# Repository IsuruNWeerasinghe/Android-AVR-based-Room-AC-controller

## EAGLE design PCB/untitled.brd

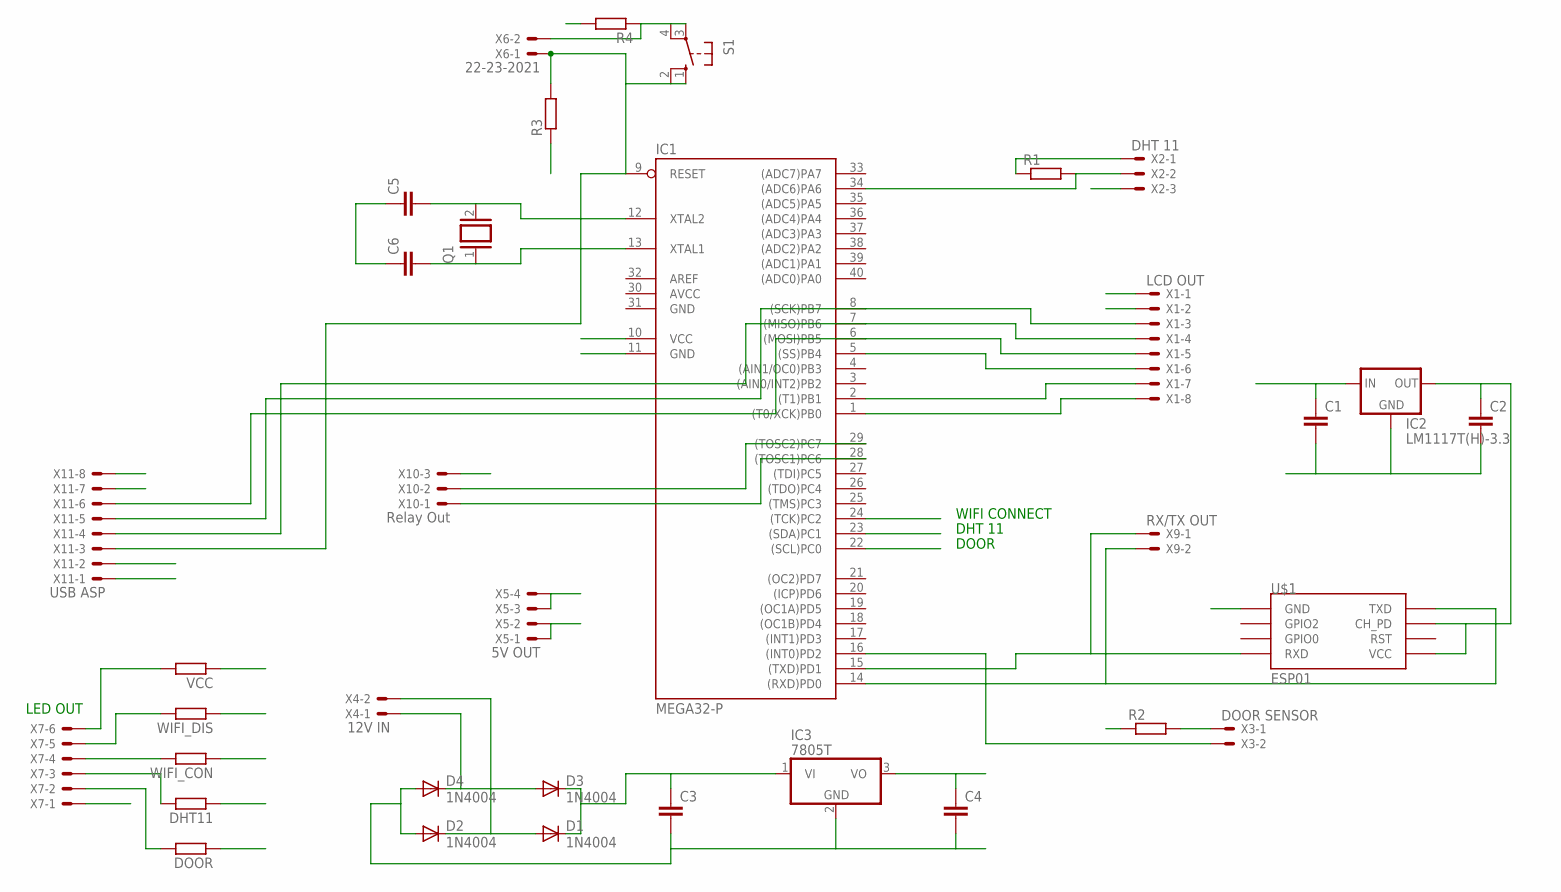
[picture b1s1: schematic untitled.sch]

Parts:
C1, C2, C4: C2.5/2; C2.5-2
C3: C5/2.5; C5B2.5
C5, C6: C-EU025-025X050; C025-025X050
D1, D2, D3, D4: 1N4004; DO41-10
DHT11: R-EU_0204/7; 0204/7
DOOR: R-EU_0204/7; 0204/7
IC1: MEGA32-P; DIL40
IC2: LM1117T(H)-3.3; TO220H
IC3: 7805T; TO220H
Q1: XTAL/S; QS
R1, R2, R3, R4: R-EU_0204/7; 0204/7
S1: 10-XX; B3F-10XX
U$1: ESP01
VCC: R-EU_0204/7; 0204/7
WIFI_CON: R-EU_0204/7; 0204/7
WIFI_DIS: R-EU_0204/7; 0204/7
X1: LCD OUT; 22-23-2081
X2: DHT 11; 22-23-2031
X3: DOOR SENSOR; 22-23-2021
X4: 12V IN; 22-23-2021
X5: 5V OUT; 22-23-2041
X6: 22-23-2021
X7: 22-23-2061
X9: RX/TX OUT; 22-23-2021
X10: Relay Out; 22-23-2031
X11: USB ASP; 22-23-2081

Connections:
12LINE1: D3.A, D4.C, X4.1
12LINE2: D1.A, D2.C, X4.2
AVCC: IC1.30 (AVCC)
DHT11: DHT11.1, IC1.23 ((SDA)PC1)
DOOR: DOOR.1, IC1.22 ((SCL)PC0)
GND: C1.2, C2.2, C3.2, C4.2, C5.1, C6.1, D2.A, D4.A, IC1.11 (GND), IC1.31 (GND), IC2.1 (GND), IC3.2 (GND), R3.1, U$1.GND, X1.2, X2.3, X5.1, X5.2, X7.1, X10.3, X11.7
unnamed: IC1.8 ((SCK)PB7), X1.3, X11.5
unnamed: IC1.7 ((MISO)PB6), X1.4, X11.4
unnamed: IC1.6 ((MOSI)PB5), X1.5, X11.6
unnamed: IC1.5 ((SS)PB4), X1.6
unnamed: IC1.2 ((T1)PB1), X1.7
unnamed: IC1.1 ((T0/XCK)PB0), X1.8
unnamed: IC1.34 ((ADC6)PA6), R1.2, X2.2
unnamed: R2.2, X3.1
unnamed: IC1.9 (RESET), R3.2, S1.1 (S), S1.2 (S1), X6.1, X11.3
unnamed: IC1.16 ((INT0)PD2), X3.2
unnamed: IC1.28 ((TOSC1)PC6), X10.1
unnamed: IC1.29 ((TOSC2)PC7), X10.2
unnamed: C2.1, IC2.2 (OUT), U$1.CH_PD, U$1.VCC
unnamed: C5.2, IC1.12 (XTAL2), Q1.2
unnamed: C6.2, IC1.13 (XTAL1), Q1.1
unnamed: C3.1, D1.C, D3.C, IC3.1 (VI)
unnamed: VCC.2, X7.6
unnamed: WIFI_DIS.2, X7.5
unnamed: WIFI_CON.2, X7.4
unnamed: DHT11.2, X7.3
unnamed: DOOR.2, X7.2
unnamed: R4.1, S1.3, S1.4 (P1), X6.2
RXD: IC1.14 ((RXD)PD0), U$1.TX (TXD), X9.2, X11.2
TXD: IC1.15 ((TXD)PD1), U$1.RX (RXD), X9.1, X11.1
VCC: C1.1, C4.1, IC1.10 (VCC), IC2.3 (IN), IC3.3 (VO), R1.1, R2.1, R4.2, VCC.1, WIFI_DIS.1, X1.1, X2.1, X5.3, X5.4, X11.8
WIFI: IC1.24 ((TCK)PC2), WIFI_CON.1

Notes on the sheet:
WIFI CONNECT
DHT 11
DOOR
LED OUT

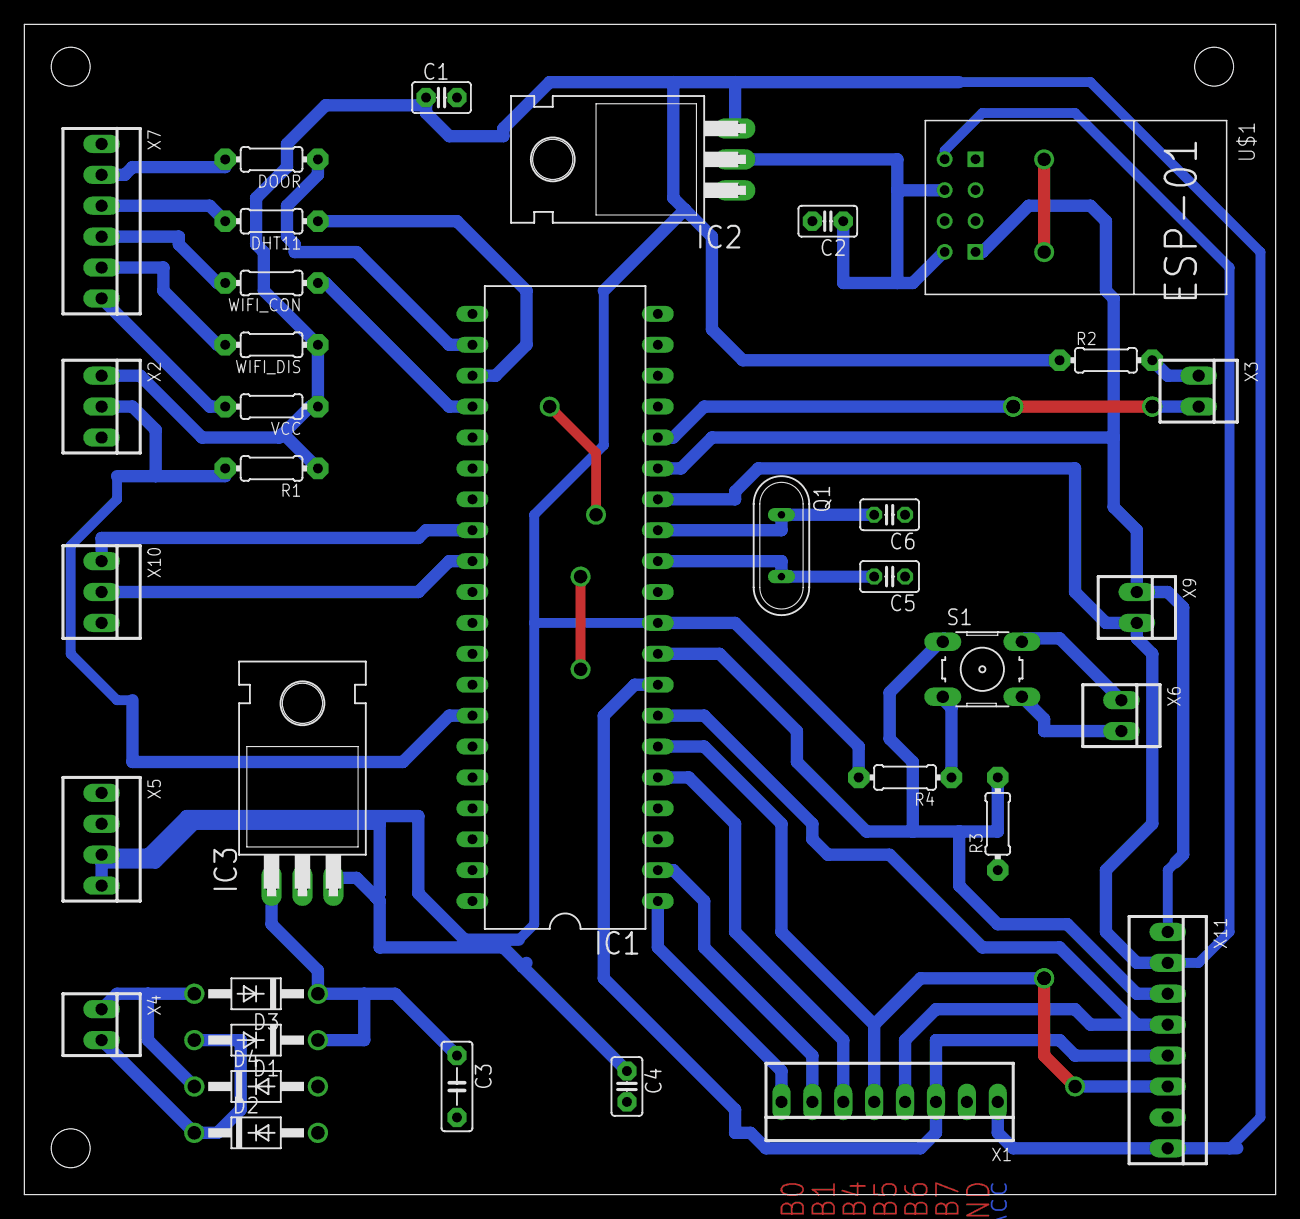
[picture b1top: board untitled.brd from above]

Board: 2 copper layers, 102.9 x 96.2 mm, 35 parts (0 on the bottom side), 31 nets.

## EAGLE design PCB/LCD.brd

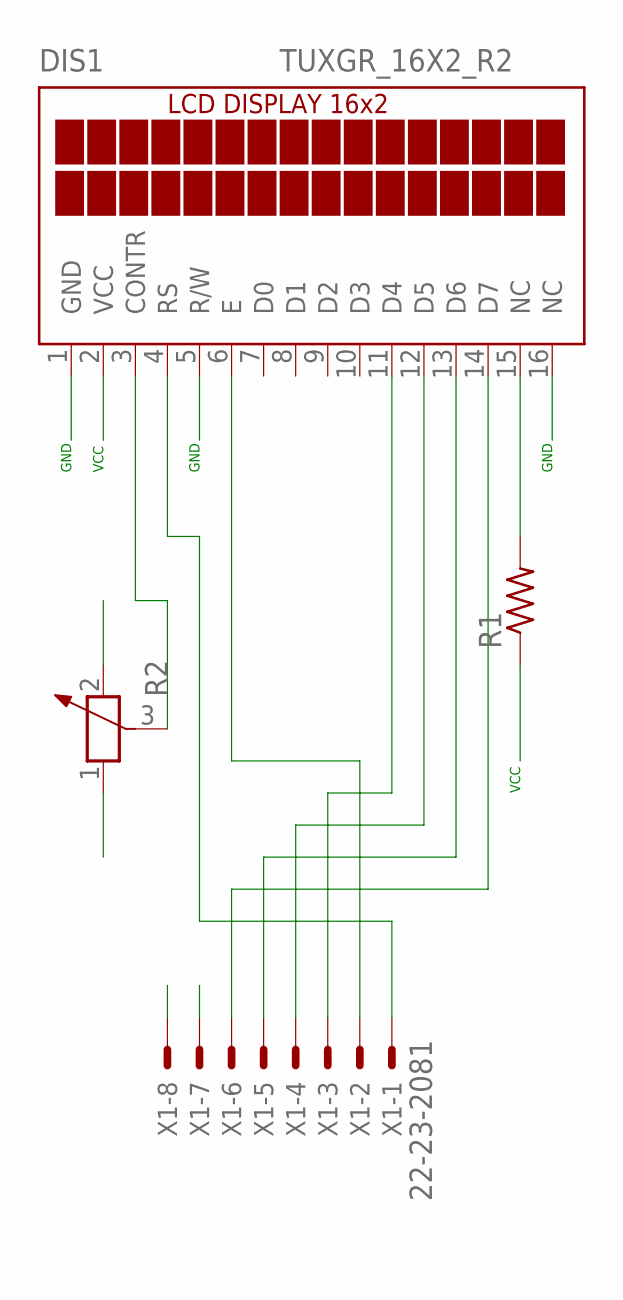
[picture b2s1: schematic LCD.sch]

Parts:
DIS1: TUXGR_16X2_R2
R1: R-US_0204/7; 0204/7
R2: POTENTIOMETER_PT-10; PT-10
X1: 22-23-2081

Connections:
GND: DIS1.1 (GND), DIS1.5 (R/W), DIS1.16 (NC), R2.1, X1.7
unnamed: DIS1.3 (CONTR), R2.3
unnamed: DIS1.15 (NC), R1.2
unnamed: DIS1.14 (D7), X1.6
unnamed: DIS1.13 (D6), X1.5
unnamed: DIS1.12 (D5), X1.4
unnamed: DIS1.11 (D4), X1.3
unnamed: DIS1.6 (E), X1.2
unnamed: DIS1.4 (RS), X1.1
VCC: DIS1.2 (VCC), R1.1, R2.2, X1.8

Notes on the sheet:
GND
VCC

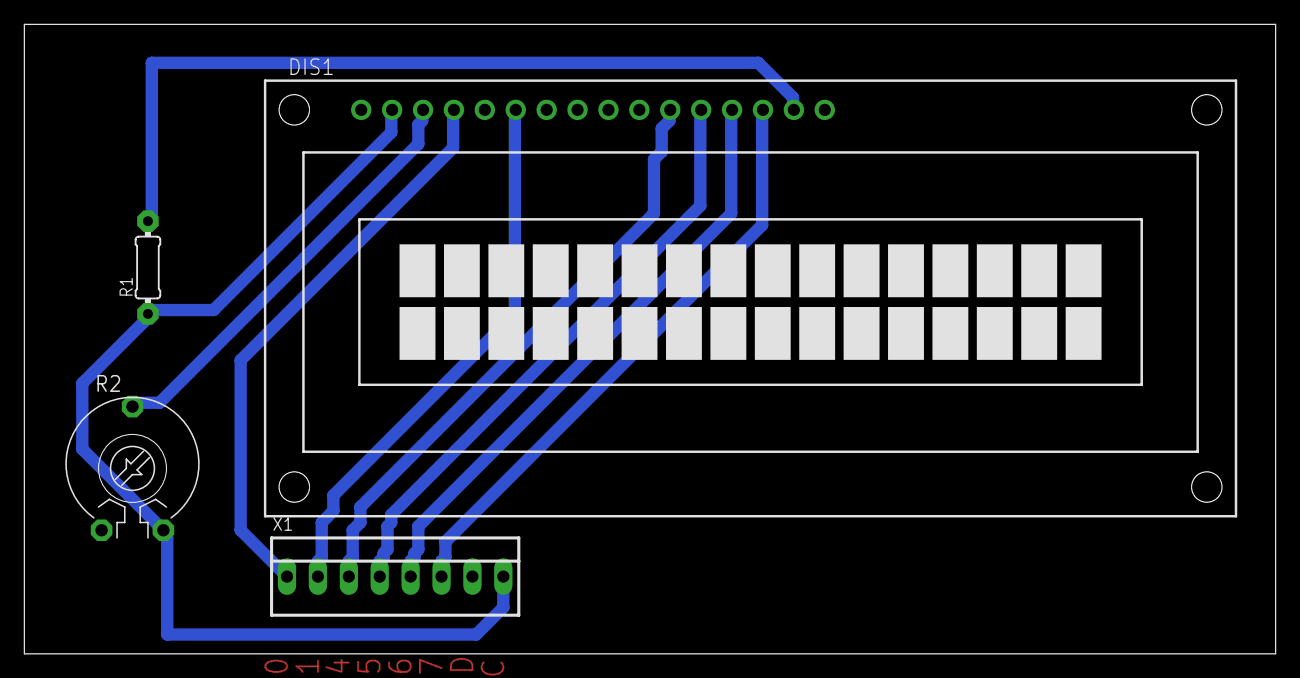
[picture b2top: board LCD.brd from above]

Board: 2 copper layers, 102.8 x 51.7 mm, 4 parts (0 on the bottom side), 10 nets.

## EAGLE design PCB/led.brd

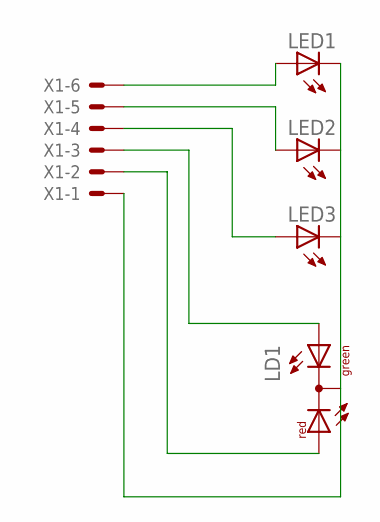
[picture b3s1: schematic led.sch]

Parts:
LD1: DUOLED-RG-C; DUOLED-C-5MM
LED1, LED2, LED3: LED5MM
X1: 22-23-2061

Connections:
GND: LD1.C, LED1.K (C), LED2.K (C), LED3.K (C), X1.1
unnamed: LED1.A, X1.6
unnamed: LED2.A, X1.5
unnamed: LED3.A, X1.4
unnamed: LD1.AX (AG), X1.3
unnamed: LD1.AR, X1.2

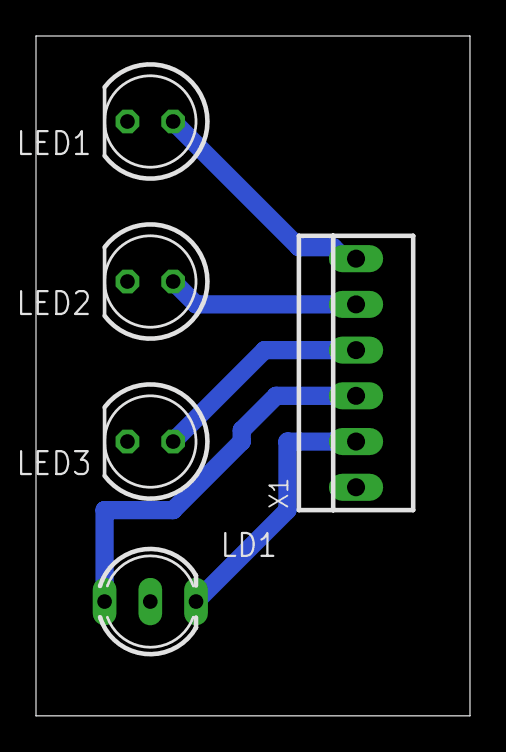
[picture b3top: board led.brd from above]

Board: 2 copper layers, 24.1 x 37.8 mm, 5 parts (0 on the bottom side), 6 nets.

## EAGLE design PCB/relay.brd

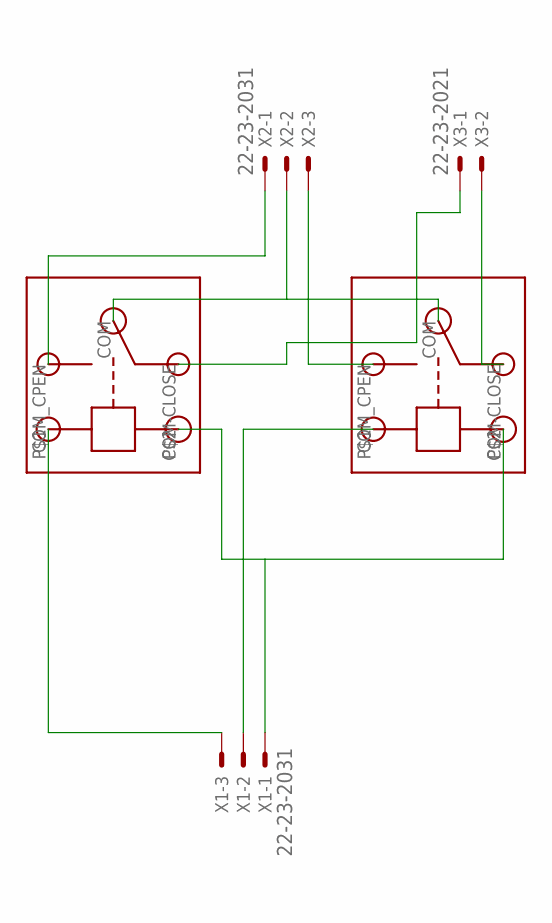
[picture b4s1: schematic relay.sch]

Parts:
U$1, U$2: RELAY
X1, X2: 22-23-2031
X3: 22-23-2021

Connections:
GND: U$1.P$2 (GND), U$2.P$2 (GND), X1.1
unnamed: U$1.P$1 (IN), X1.3
unnamed: U$2.P$1 (IN), X1.2
unnamed: U$1.COM-CLOSE, X3.1
unnamed: U$1.COM_CPEN (COM-OPEN), X2.1
unnamed: U$2.COM_CPEN (COM-OPEN), X2.3
unnamed: U$1.COM, U$2.COM, X2.2
unnamed: U$2.COM-CLOSE, X3.2

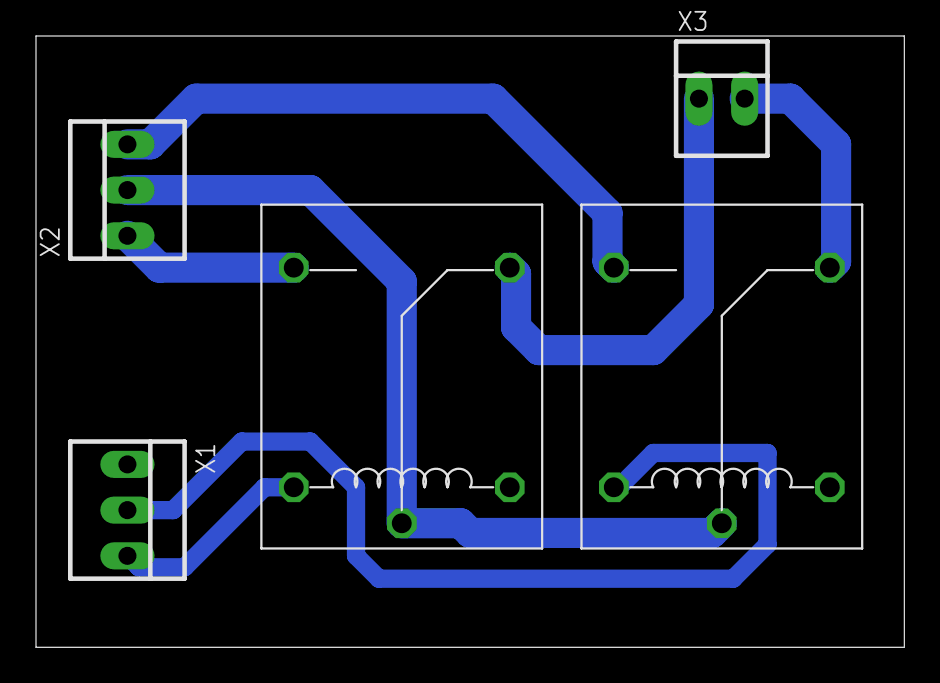
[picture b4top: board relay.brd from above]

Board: 2 copper layers, 48.2 x 34.0 mm, 5 parts (0 on the bottom side), 8 nets.

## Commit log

2020-07-07 room temp
